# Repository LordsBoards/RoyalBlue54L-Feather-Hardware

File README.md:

# RoyalBlue54L Feather

An ARM + RISC-V Feather board with the new nRF54L15, built-in debugger, and smart PMIC

## Overview

The RoyalBlue54L--familiar Feather formfactor with distinctive features. Nordic's next-gen nRF54L15, an onboard CMSIS-DAP debugger + UART bridge, and smart power-management features from the nPM1300 enable rapid development for your next Bluetooth 6.0, Thread, Matter, Zigbee, Amazon Sidewalk, or proprietary wireless project.

Pre-launch on Crowd Supply - More details coming soon!

## Hardware Features

* Dual-core processing power:
  * ARM Cortex-M33 at 128MHz
  * RISC-V co-processor at 128MHz
* Comprehensive memory configuration:
  * 1.5MB of non-volatile memory (NVM)
  * 256KB of RAM
  * 2MB external flash
* Advanced wireless capabilities:
  * BLE 6.0 support with channel sounding for distance estimation
  * 4Mbps PHY for proprietary wireless protocols
  * 30-50% power reduction compared to nRF52 series
* Integrated development tools:
  * CMSIS-DAP debugger (nRF52833-based)
  * USB-to-UART bridge
  * Open source, Zephyr RTOS-based firmware
* Smart power management:
  * USB-C charging up to 800mA with nPM1300
  * High-accuracy battery fuel gauge
* Connectivity:
  * JST-PH connector
  * STEMMA-QT/Qwiic port
  * NFC antenna connector
* User interfaces:
  * User LED
  * RGB LED (nPM1300-driven)
  * User button
  * Reset button

## Repository Contents

This repository contains the hardware design files for the RoyalBlue54L Feather. The board is designed with KiCAD and includes:

* Schematic files
* PCB layout
* Bill of Materials (BOM)
* Manufacturing files
* Documentation

## Pinout

## Related Repositories

* [Zephyr Board Support](https://github.com/LordsBoards/RoyalBlue-nRF54L15-Zephyr-Boards)
* [Debugger Firmware](https://github.com/LordsBoards/RoyalBlue-nRF54L15-Debugger-Firmware)

## License

Hardware files are released under CERN-OHL-V2-P.

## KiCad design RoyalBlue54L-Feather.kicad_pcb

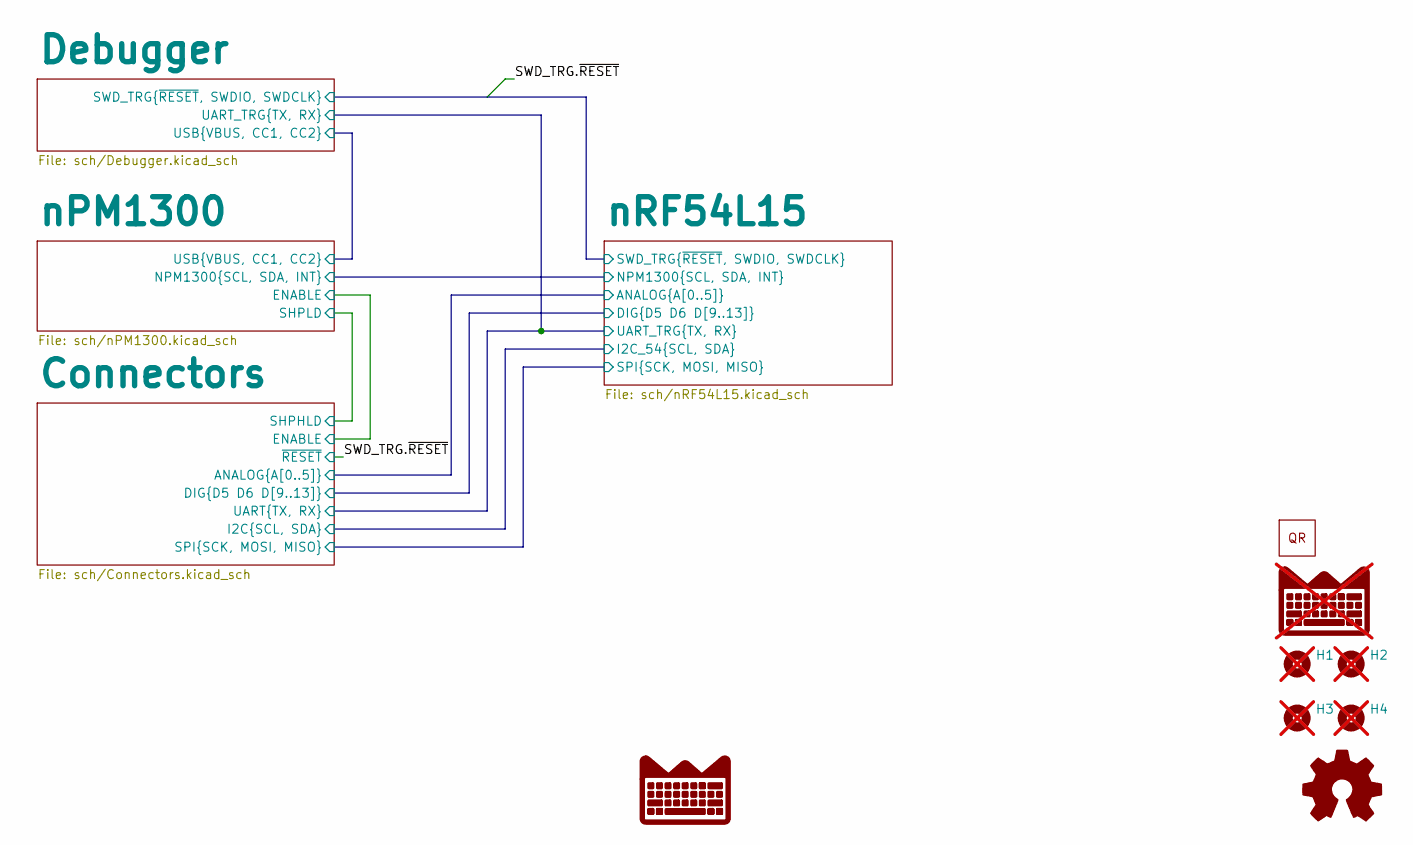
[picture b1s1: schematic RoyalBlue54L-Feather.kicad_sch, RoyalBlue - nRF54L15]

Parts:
H1, H2, H3, H4: MountingHole; MountingHole_2.5mm; not fitted
LOGO1: LordsBoardsLogo_Small_Silk; not fitted
U7: RoyalBlue54L_QRCode

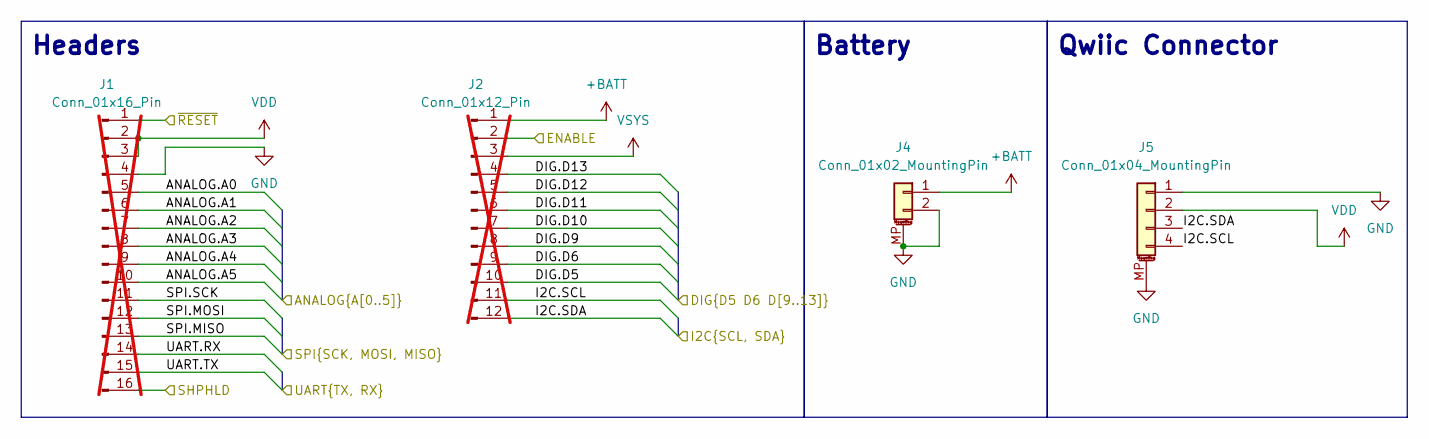
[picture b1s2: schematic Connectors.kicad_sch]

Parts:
J1: Conn_01x16_Pin; PinHeader_1x16_P2.54mm_Vertical; not fitted
J2: Conn_01x12_Pin; PinHeader_1x12_P2.54mm_Vertical; not fitted
J4: Conn_01x02_MountingPin; JST_PH_S2B-PH-SM4-TB_1x02-1MP_P2.00mm_Horizontal; LCSC C295747
J5: Conn_01x04_MountingPin; JST_SH_SM04B-SRSS-TB_1x04-1MP_P1.00mm_Horizontal; LCSC C3029343

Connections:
+BATT: J2.1, J4.1; also elsewhere on the board
/Connectors/ANALOG.A0: J1.5; also elsewhere on the board
/Connectors/ANALOG.A1: J1.6; also elsewhere on the board
/Connectors/ANALOG.A2: J1.7; also elsewhere on the board
/Connectors/ANALOG.A3: J1.8; also elsewhere on the board
/Connectors/ANALOG.A4: J1.9; also elsewhere on the board
/Connectors/ANALOG.A5: J1.10; also elsewhere on the board
/Connectors/DIG.D5: J2.10; also elsewhere on the board
/Connectors/DIG.D6: J2.9; also elsewhere on the board
/Connectors/DIG.D9: J2.8; also elsewhere on the board
/Connectors/DIG.D10: J2.7; also elsewhere on the board
/Connectors/DIG.D11: J2.6; also elsewhere on the board
/Connectors/DIG.D12: J2.5; also elsewhere on the board
/Connectors/DIG.D13: J2.4; also elsewhere on the board
/Connectors/ENABLE: J2.2; also elsewhere on the board
/Connectors/I2C.SCL: J2.11, J5.4; also elsewhere on the board
/Connectors/I2C.SDA: J2.12, J5.3; also elsewhere on the board
/Connectors/SHPHLD: J1.16; also elsewhere on the board
/Connectors/SPI.MISO: J1.13; also elsewhere on the board
/Connectors/SPI.MOSI: J1.12; also elsewhere on the board
/Connectors/SPI.SCK: J1.11; also elsewhere on the board
/Connectors/UART.RX: J1.14; also elsewhere on the board
/Connectors/UART.TX: J1.15; also elsewhere on the board
/Debugger/SWD_TRG.~RESET: J1.1; also elsewhere on the board
GND: J1.4, J4.2, J4.MP (MountPin), J5.1, J5.MP (MountPin); also elsewhere on the board
VDD: J1.2, J1.3, J5.2; also elsewhere on the board
VSYS: J2.3; also elsewhere on the board

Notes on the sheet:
Qwiic Connector
Battery
Headers

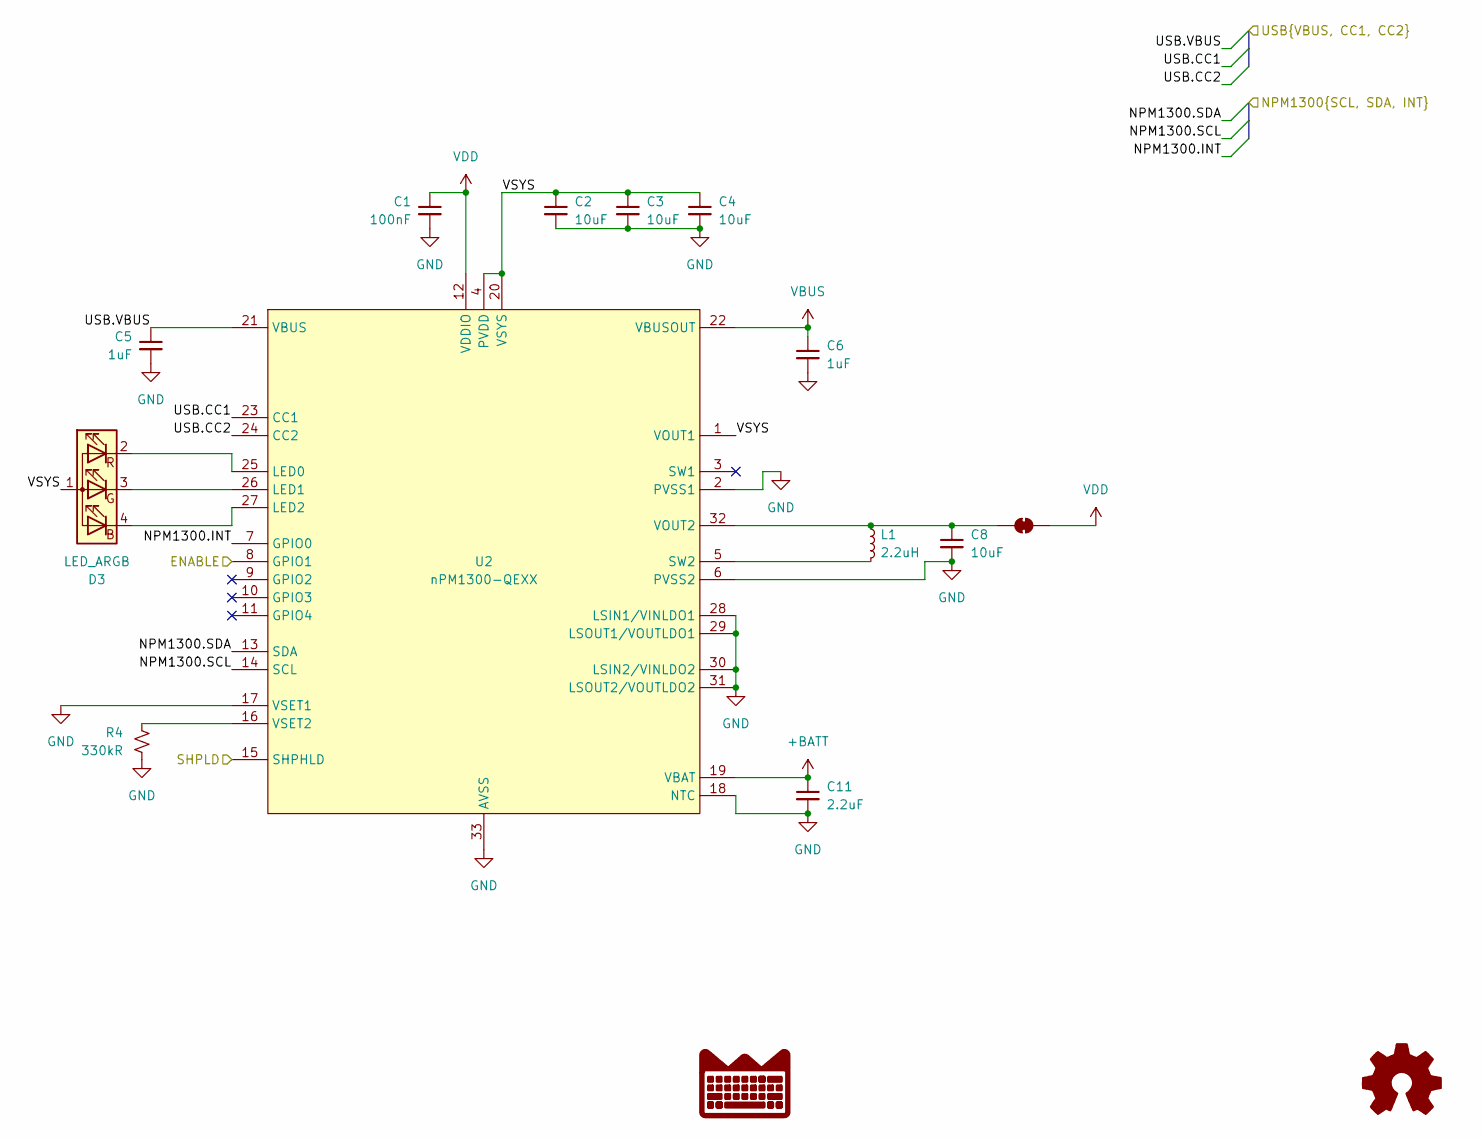
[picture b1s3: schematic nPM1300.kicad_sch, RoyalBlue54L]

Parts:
C1: 100nF; C_0402_1005Metric; LCSC C307331
C2, C3, C4, C8: 10uF; C_0603_1608Metric; LCSC C96446
C5, C6: 1uF; C_0603_1608Metric; LCSC C15849
C11: 2.2uF; C_0603_1608Metric; LCSC C23630
D3: LED_ARGB; LED_Wurth_150044M155260; LCSC C404280
JP1: SolderJumper_2_Bridged; SolderJumper-2_P1.3mm_Bridged_RoundedPad1.0x1.5mm
L1: 2.2uH; L_0603_1608Metric; LCSC C337910
R4: 330kR; R_0402_1005Metric; LCSC C25778
U2: nPM1300-QEXX; QFN-32-1EP_5x5mm_P0.5mm_EP3.6x3.6mm_ThermalVias; LCSC C7466043

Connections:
+BATT: C11.1, U2.19 (VBAT); also elsewhere on the board
/Connectors/ENABLE: U2.8 (GPIO1); also elsewhere on the board
/Connectors/SHPHLD: U2.15 (SHPHLD); also elsewhere on the board
/Debugger/USB.CC1: U2.23 (CC1); also elsewhere on the board
/Debugger/USB.CC2: U2.24 (CC2); also elsewhere on the board
/Debugger/USB.VBUS: C5.1, U2.21 (VBUS); also elsewhere on the board
/nPM1300/NPM1300.INT: U2.7 (GPIO0); also elsewhere on the board
/nPM1300/NPM1300.SCL: U2.14 (SCL); also elsewhere on the board
/nPM1300/NPM1300.SDA: U2.13 (SDA); also elsewhere on the board
GND: C1.2, C2.2, C3.2, C4.2, C5.2, C6.2, C8.2, C11.2, R4.2, U2.2 (PVSS1), U2.6 (PVSS2), U2.17 (VSET1), U2.18 (NTC), U2.28 (LSIN1/VINLDO1), U2.29 (LSOUT1/VOUTLDO1), U2.30 (LSIN2/VINLDO2), U2.31 (LSOUT2/VOUTLDO2), U2.33 (AVSS); also elsewhere on the board
unnamed: D3.4 (BK), U2.27 (LED2)
unnamed: D3.3 (GK), U2.26 (LED1)
unnamed: D3.2 (RK), U2.25 (LED0)
unnamed: C8.1, JP1.1 (A), L1.1, U2.32 (VOUT2)
unnamed: L1.2, U2.5 (SW2)
unnamed: R4.1, U2.16 (VSET2)
VBUS: C6.1, U2.22 (VBUSOUT); also elsewhere on the board
VDD: C1.1, JP1.2 (B), U2.12 (VDDIO); also elsewhere on the board
VSYS: C2.1, C3.1, C4.1, D3.1 (A), U2.1 (VOUT1), U2.4 (PVDD), U2.20 (VSYS); also elsewhere on the board

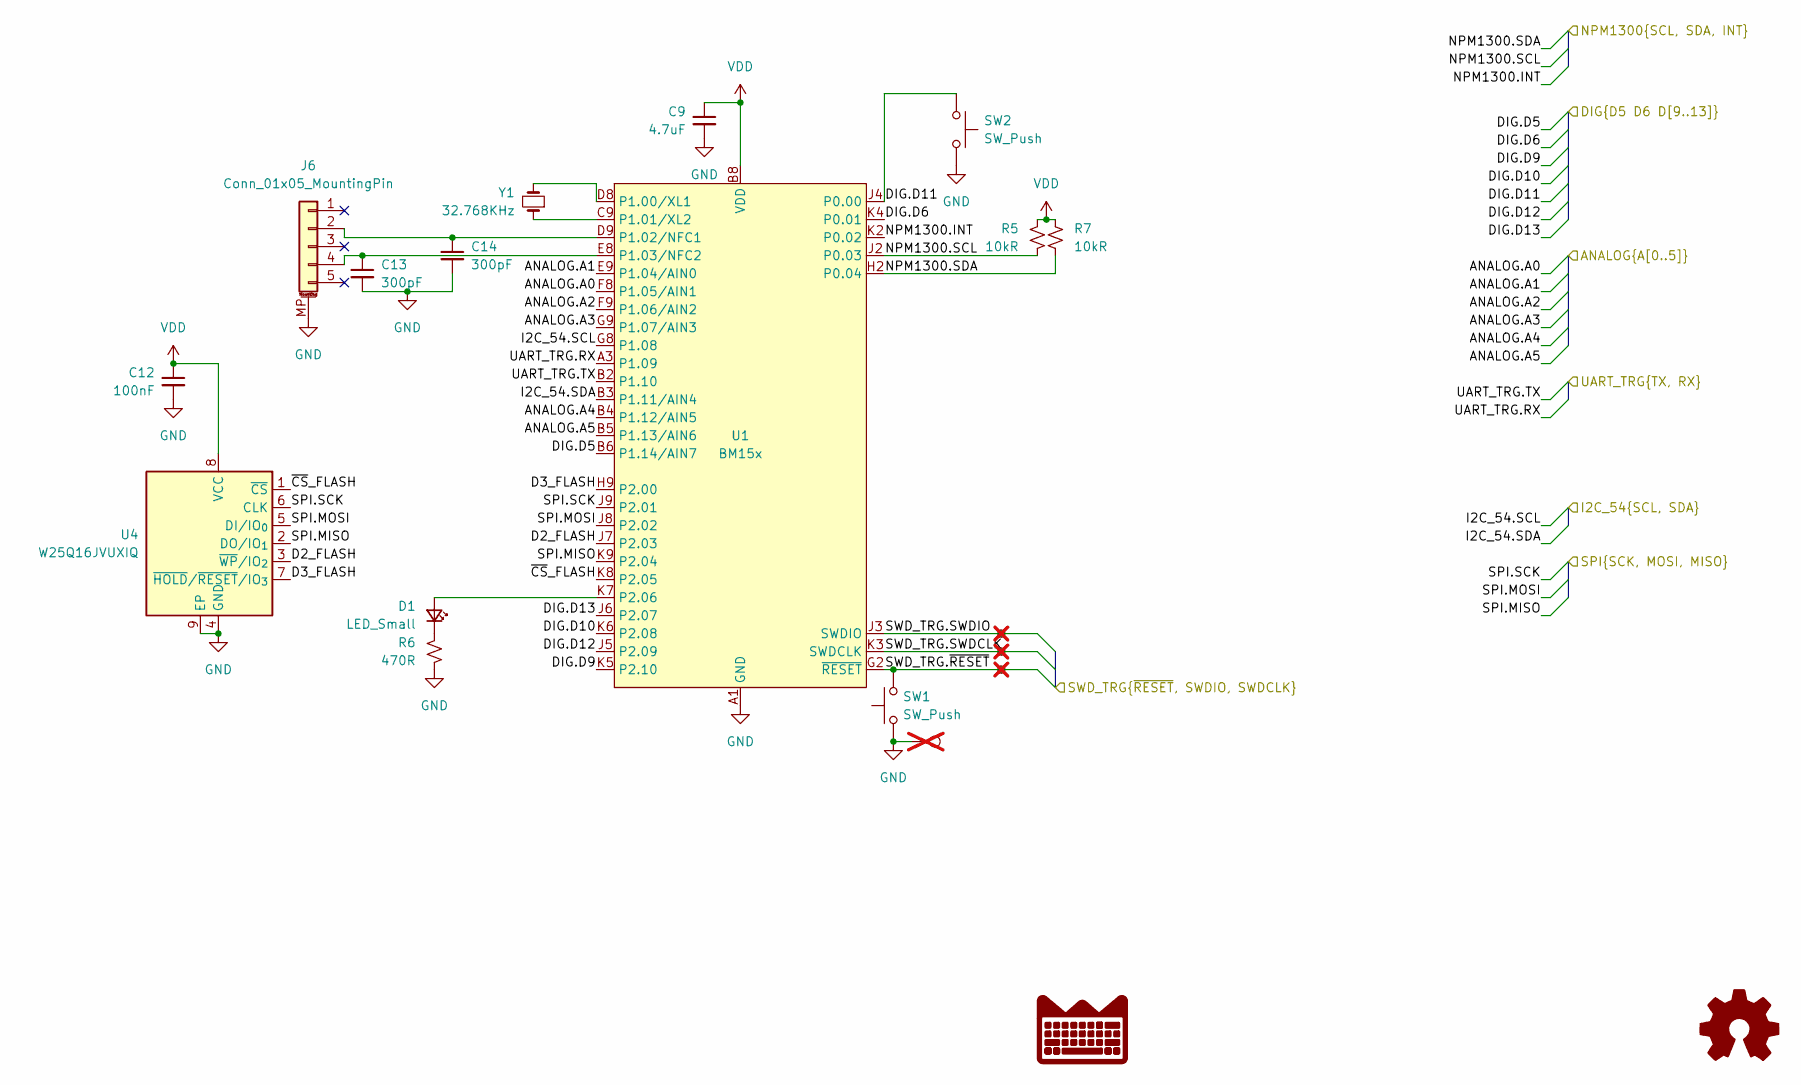
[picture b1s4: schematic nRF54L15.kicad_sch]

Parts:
C9: 4.7uF; C_0402_1005Metric; LCSC C23733
C12: 100nF; C_0402_1005Metric; LCSC C307331
C13, C14: 300pF; C_0402_1005Metric; LCSC C126505
D1: LED_Small; LED_0603_1608Metric; LCSC C125103
J6: Conn_01x05_MountingPin; CONN-SMD_5P-P0.50_HCTL_HC-FPC-05-09-5RLTAG; LCSC C5213747
R5, R7: 10kR; R_0402_1005Metric; LCSC C25744
R6: 470R; R_0402_1005Metric; LCSC C25117
SW1, SW2: SW_Push; SW_Push_1P1T_NO_Vertical_Wuerth_434133025816; LCSC C139797
TP1, TP2, TP3, TP4: TestPoint; TestPoint_Pad_D2.0mm; not fitted
U1: BM15x; BM15x-LGA-45_15.8x10mm; LCSC C9900148376
U4: W25Q16JVUXIQ; Winbond_USON-8-1EP_3x2mm_P0.5mm_EP0.2x1.6mm; LCSC C2843335
Y1: 32.768KHz; Crystal_SMD_3215-2Pin_3.2x1.5mm; LCSC C32346

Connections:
/Connectors/ANALOG.A0: U1.F8 (P1.05/AIN1); also elsewhere on the board
/Connectors/ANALOG.A1: U1.E9 (P1.04/AIN0); also elsewhere on the board
/Connectors/ANALOG.A2: U1.F9 (P1.06/AIN2); also elsewhere on the board
/Connectors/ANALOG.A3: U1.G9 (P1.07/AIN3); also elsewhere on the board
/Connectors/ANALOG.A4: U1.B4 (P1.12/AIN5); also elsewhere on the board
/Connectors/ANALOG.A5: U1.B5 (P1.13/AIN6); also elsewhere on the board
/Connectors/DIG.D5: U1.B6 (P1.14/AIN7); also elsewhere on the board
/Connectors/DIG.D6: U1.K4 (P0.01); also elsewhere on the board
/Connectors/DIG.D9: U1.K5 (P2.10); also elsewhere on the board
/Connectors/DIG.D10: U1.K6 (P2.08); also elsewhere on the board
/Connectors/DIG.D11: SW2.1, U1.J4 (P0.00); also elsewhere on the board
/Connectors/DIG.D12: U1.J5 (P2.09); also elsewhere on the board
/Connectors/DIG.D13: U1.J6 (P2.07); also elsewhere on the board
/Connectors/I2C.SCL: U1.G8 (P1.08); also elsewhere on the board
/Connectors/I2C.SDA: U1.B3 (P1.11/AIN4); also elsewhere on the board
/Connectors/SPI.MISO: U1.K9 (P2.04), U4.2 (DO/IO_{1}); also elsewhere on the board
/Connectors/SPI.MOSI: U1.J8 (P2.02), U4.5 (DI/IO_{0}); also elsewhere on the board
/Connectors/SPI.SCK: U1.J9 (P2.01), U4.6 (CLK); also elsewhere on the board
/Connectors/UART.RX: U1.A3 (P1.09); also elsewhere on the board
/Connectors/UART.TX: U1.B2 (P1.10); also elsewhere on the board
/Debugger/SWD_TRG.SWDCLK: TP3.1, U1.K3 (SWDCLK); also elsewhere on the board
/Debugger/SWD_TRG.SWDIO: TP1.1, U1.J3 (SWDIO); also elsewhere on the board
/Debugger/SWD_TRG.~RESET: SW1.2, TP2.1, U1.G2 (~RESET); also elsewhere on the board
/nPM1300/NPM1300.INT: U1.K2 (P0.02); also elsewhere on the board
/nPM1300/NPM1300.SCL: R5.2, U1.J2 (P0.03); also elsewhere on the board
/nPM1300/NPM1300.SDA: R7.2, U1.H2 (P0.04); also elsewhere on the board
/nRF54L15/D2_FLASH: U1.J7 (P2.03), U4.3 (~WP/IO_{2})
/nRF54L15/D3_FLASH: U1.H9 (P2.00), U4.7 (~HOLD/~RESET/IO_{3})
/nRF54L15/~CS_FLASH: U1.K8 (P2.05), U4.1 (~CS)
GND: C9.2, C12.2, C13.2, C14.2, J6.MP (MountPin), R6.2, SW1.1, SW2.2, TP4.1, U1.A1 (GND), U1.A9 (GND), U1.B1 (GND), U1.B7 (GND), U1.B9 (GND), U1.D1 (GND), U1.E1 (GND), U1.F1 (GND), U1.H8 (GND), U4.4 (GND), U4.9 (EP); also elsewhere on the board
unnamed: D1.2 (A), U1.K7 (P2.06)
unnamed: D1.1 (K), R6.1
unnamed: C14.1, J6.2, U1.D9 (P1.02/NFC1)
unnamed: C13.1, J6.4, U1.E8 (P1.03/NFC2)
unnamed: U1.D8 (P1.00/XL1), Y1.2
unnamed: U1.C9 (P1.01/XL2), Y1.1
VDD: C9.1, C12.1, R5.1, R7.1, U1.B8 (VDD), U1.C8 (VDD), U4.8 (VCC); also elsewhere on the board

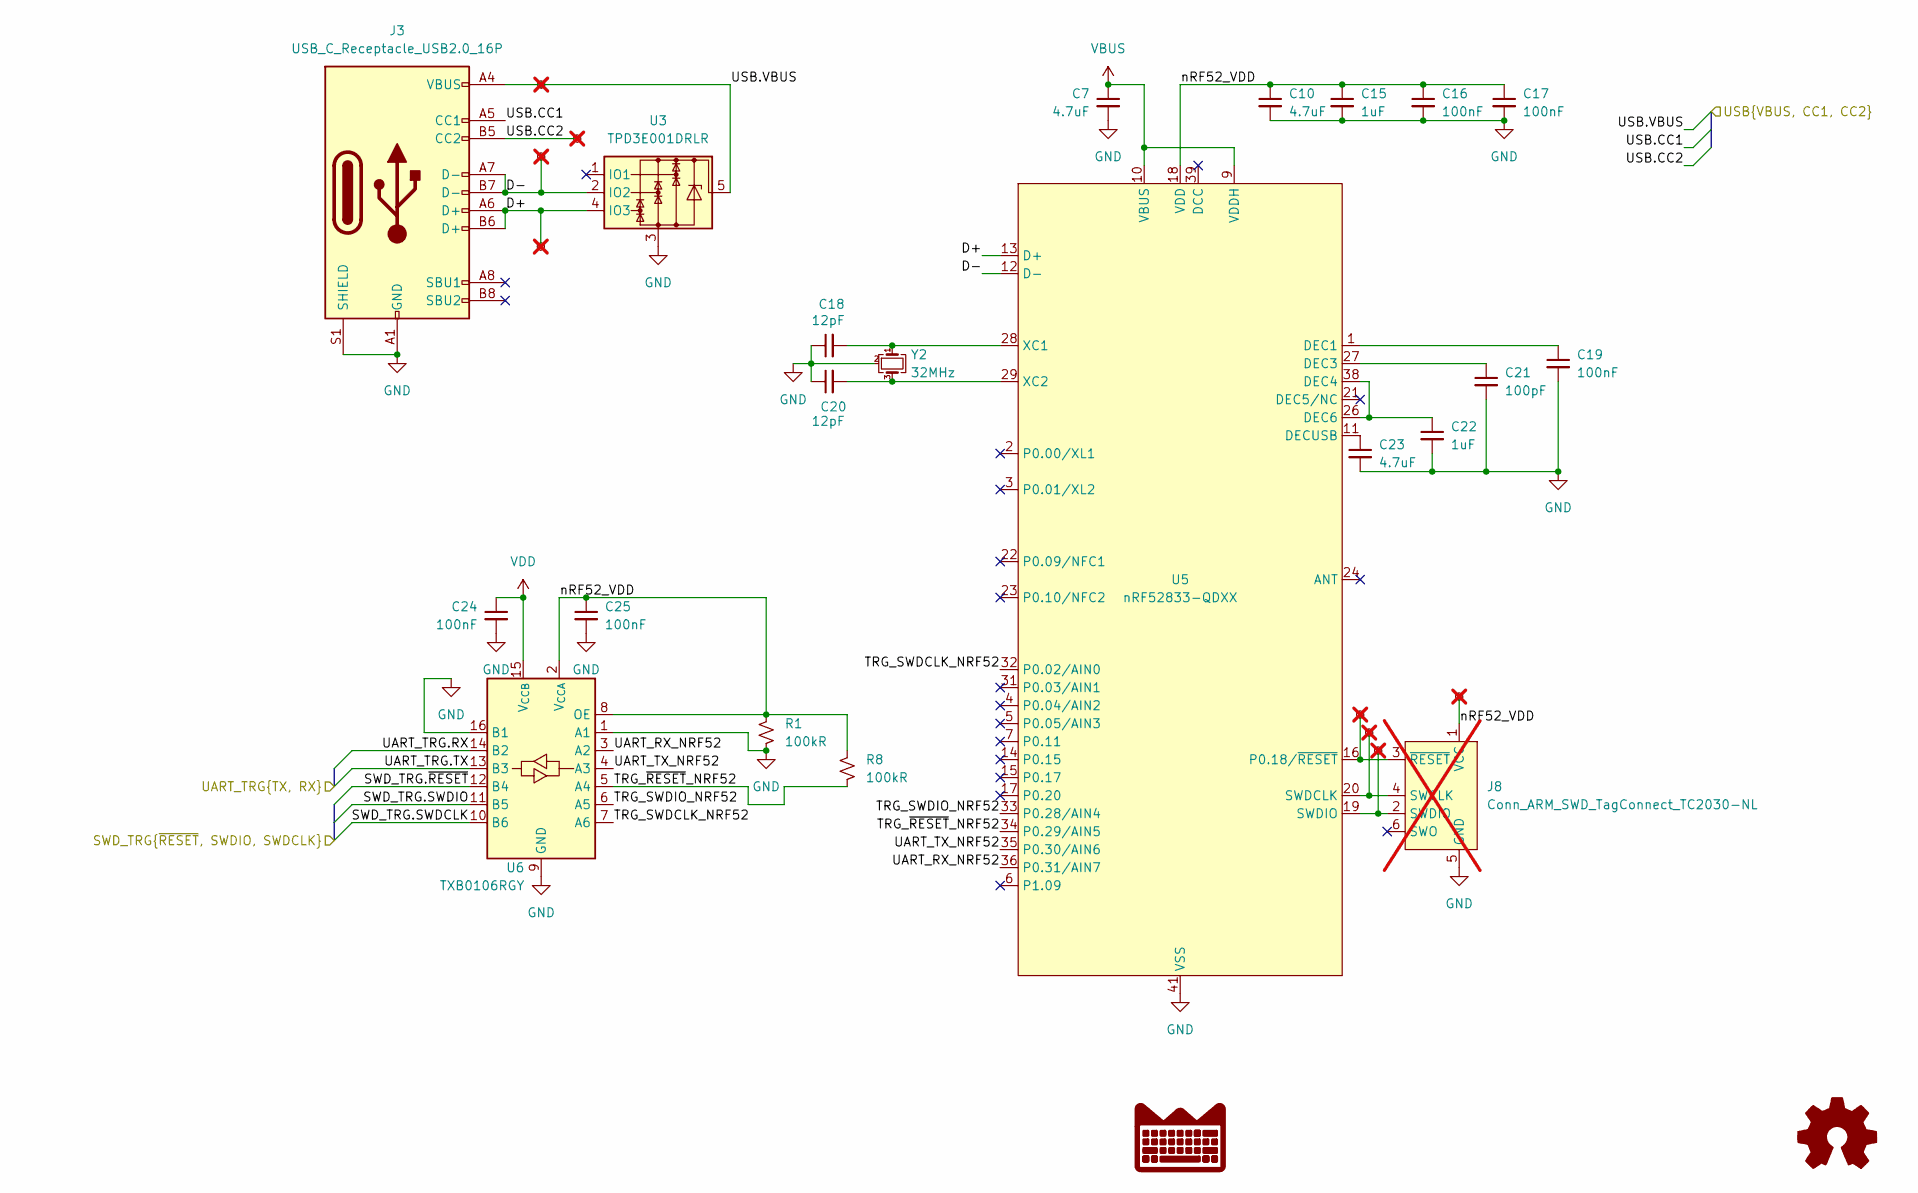
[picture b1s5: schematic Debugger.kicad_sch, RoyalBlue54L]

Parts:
C7, C10, C23: 4.7uF; C_0402_1005Metric; LCSC C23733
C15, C22: 1uF; C_0402_1005Metric; LCSC C52923
C16, C17, C19, C24, C25: 100nF; C_0402_1005Metric; LCSC C307331
C18, C20: 12pF; C_0402_1005Metric; LCSC C1547
C21: 100pF; C_0402_1005Metric; LCSC C1546
J3: USB_C_Receptacle_USB2.0_16P; USB_C_Receptacle_HRO_TYPE-C-31-M-12; LCSC C165948
J8: Conn_ARM_SWD_TagConnect_TC2030-NL; Tag-Connect_TC2030-IDC-NL_2x03_P1.27mm_Vertical; not fitted
R1, R8: 100kR; R_0402_1005Metric; LCSC C25741
TP5, TP6, TP7, TP8, TP9, TP10, TP11, TP12: TestPoint; TestPoint_Pad_D1.5mm; not fitted
U3: TPD3E001DRLR; SOT-553; LCSC C2999113
U5: nRF52833-QDXX; QFN-40-1EP_5x5mm_P0.4mm_EP3.6x3.6mm_ThermalVias; LCSC C2895249
U6: TXB0106RGY; Texas_RGY_R-PVQFN-N16_EP2.05x2.55mm; LCSC C2652978
Y2: 32MHz; Crystal_SMD_2016-4Pin_2.0x1.6mm; LCSC C2682773

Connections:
/Connectors/UART.RX: U6.14 (B2); also elsewhere on the board
/Connectors/UART.TX: U6.13 (B3); also elsewhere on the board
/Debugger/D+: J3.A6 (D+), J3.B6 (D+), TP7.1, U3.4 (IO3), U5.13 (D+)
/Debugger/D-: J3.A7 (D-), J3.B7 (D-), TP8.1, U3.2 (IO2), U5.12 (D-)
/Debugger/SWD_TRG.SWDCLK: U6.10 (B6); also elsewhere on the board
/Debugger/SWD_TRG.SWDIO: U6.11 (B5); also elsewhere on the board
/Debugger/SWD_TRG.~RESET: U6.12 (B4); also elsewhere on the board
/Debugger/TRG_SWDCLK_NRF52: U5.32 (P0.02/AIN0), U6.7 (A6)
/Debugger/TRG_SWDIO_NRF52: U5.33 (P0.28/AIN4), U6.6 (A5)
/Debugger/TRG_~RESET_NRF52: R8.2, U5.34 (P0.29/AIN5), U6.5 (A4)
/Debugger/UART_RX_NRF52: U5.36 (P0.31/AIN7), U6.3 (A2)
/Debugger/UART_TX_NRF52: U5.35 (P0.30/AIN6), U6.4 (A3)
/Debugger/USB.CC1: J3.A5 (CC1); also elsewhere on the board
/Debugger/USB.CC2: J3.B5 (CC2), TP6.1; also elsewhere on the board
/Debugger/USB.VBUS: J3.A4 (VBUS), J3.A9 (VBUS), J3.B4 (VBUS), J3.B9 (VBUS), TP5.1, U3.5; also elsewhere on the board
/Debugger/nRF52_VDD: C10.1, C15.1, C16.1, C17.1, C25.1, J8.1 (VCC), R1.1, R8.1, TP9.1, U5.8 (VDD), U5.18 (VDD), U5.30 (VDD), U5.40 (VDD), U6.2 (V_{CCA}), U6.8 (OE)
GND: C7.2, C10.2, C15.2, C16.2, C17.2, C18.1, C19.2, C20.1, C21.2, C22.2, C23.2, C24.2, C25.2, J3.A1 (GND), J3.A12 (GND), J3.B1 (GND), J3.B12 (GND), J3.S1 (SHIELD), J8.5 (GND), R1.2, U3.3, U5.25 (VSS_PA), U5.37 (VSS), U5.41 (VSS), U6.1 (A1), U6.9 (GND), U6.16 (B1), U6.17 (GND), Y2.2, Y2.4; also elsewhere on the board
unnamed: J8.4 (SWCLK), TP11.1, U5.20 (SWDCLK)
unnamed: J8.2 (SWDIO), TP12.1, U5.19 (SWDIO)
unnamed: J8.3 (~RESET), TP10.1, U5.16 (P0.18/~RESET)
unnamed: C19.1, U5.1 (DEC1)
unnamed: C21.1, U5.27 (DEC3)
unnamed: C22.1, U5.26 (DEC6), U5.38 (DEC4)
unnamed: C23.1, U5.11 (DECUSB)
unnamed: C18.2, U5.28 (XC1), Y2.1
unnamed: C20.2, U5.29 (XC2), Y2.3
VBUS: C7.1, U5.9 (VDDH), U5.10 (VBUS); also elsewhere on the board
VDD: C24.1, U6.15 (V_{CCB}); also elsewhere on the board

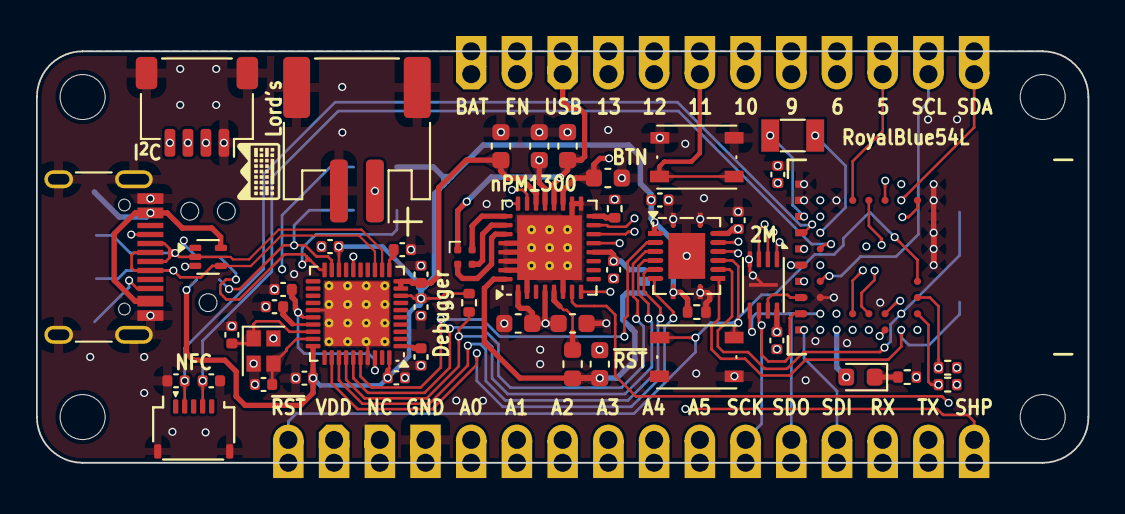
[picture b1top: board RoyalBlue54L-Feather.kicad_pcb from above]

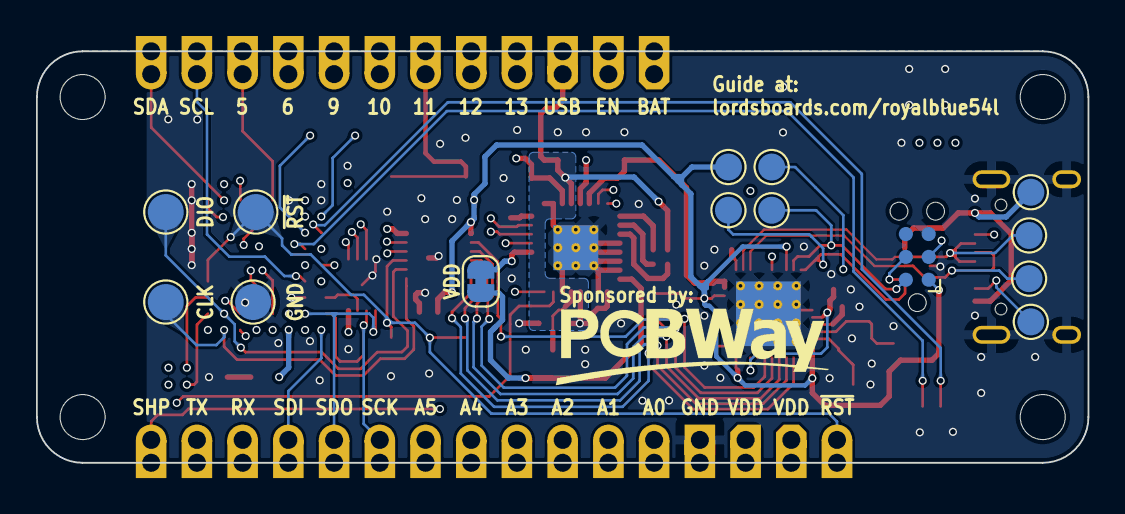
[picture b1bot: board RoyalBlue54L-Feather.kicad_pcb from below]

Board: 8 copper layers, 58.4 x 22.9 mm, 70 parts (16 on the bottom side), 68 nets.

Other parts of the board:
Ref**: Val**; PCBWayLogo

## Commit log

2025-01-26 Initial commit.
2025-02-04 Updated 02/03/25
2025-02-04 Renamed to RoyalBlue54L-Feather
2025-02-04 JLCPCB files and README
2025-02-04 Added NFC antenna hardware repo
2025-02-12 Added testpoints, moved USB connection to VSYS.
2025-02-15 Updated to include castellations, more testpoints
2025-02-17 Adjusted pinout, added pinout diagram
2025-02-17 Updated README with pinout diagram
2025-02-19 Adjusted pinout SVGs to be 16:9
2025-02-20 Revert changes to vias, DRC fixes
2025-02-20 Removed JLCPCB files
2025-02-20 Updated all vias to share size, fixed zone fill outlines
2025-02-20 Rendered svg to paths
2025-02-25 Fixed DRC errors
2025-02-26 Added PCBWay logo
